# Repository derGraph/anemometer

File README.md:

# Ultrasonic Anemometer

This project contains the circuit and code for a ultrasonic Anemometer. The anemometer works by 4 ultrasonic Transducers where 2 of them always face each other. 2 Transducers describe one Axis, so with 4 Transducers you can measure x and y Wind components. The circuit only recieves the signal and boosts a Peak-to-Peak Sine Voltage of 50mV to a Square Wave of VCC to 0V. With the microcontroller you have to compare the time difference between the output signal, a signal of 50% Duty Cycle 40kHz and the recieved signal. Then you can calibrate your sensor with 0 wind speed. In my case i measure the Clock Cycles of an ESP8266 to get a pretty precise time.

### Circuit Description

The circuit contains of a LM324 OP-Amp and an LM393 Comperator. With these 2 IC's you can archive processing for 2 Channels. after the signal is coming from the transducer it gets biased with a VCC/2 Voltage to be in a useful working range for the later components. Then the signal is fed through a voltage follower to get a low impedance signal for the next Amplifier stage. The next stage is, as said an inverting Amplifier with a gain of 10. The gain can't be to high to have a functioning amplification. As you can see if you have signal at 40kHz the maximum gain can be 10. 

After that the signal is fed into the LM393 Comparator. Keep in mind that to get the comperator to function you have to pull the output up. In the first revision of the board  (Rev 1) there are 2 Footprints of resistors too much (R5, R14) this is fixed with Rev 2.

### Modularity

In the standard configuration of the PCB 2 Channels are set up but if you have a weaker Signal you can cut the S2_EN between 1/2 and solder 2/3. By populating R17 and R18 you can transform your 1 Stage Amplifier in a 3 Stage Amplifier.
If you need an additional Filter you can cut EN_Filter and populate the Bandpass-Filter on the backside of the PCB.

### Full Circuit

The whole circuit contains 2 Channels with the logic to implement the 3 Stage Amplifier included in the lower one. Also there is power supply and connectors to the MCU.

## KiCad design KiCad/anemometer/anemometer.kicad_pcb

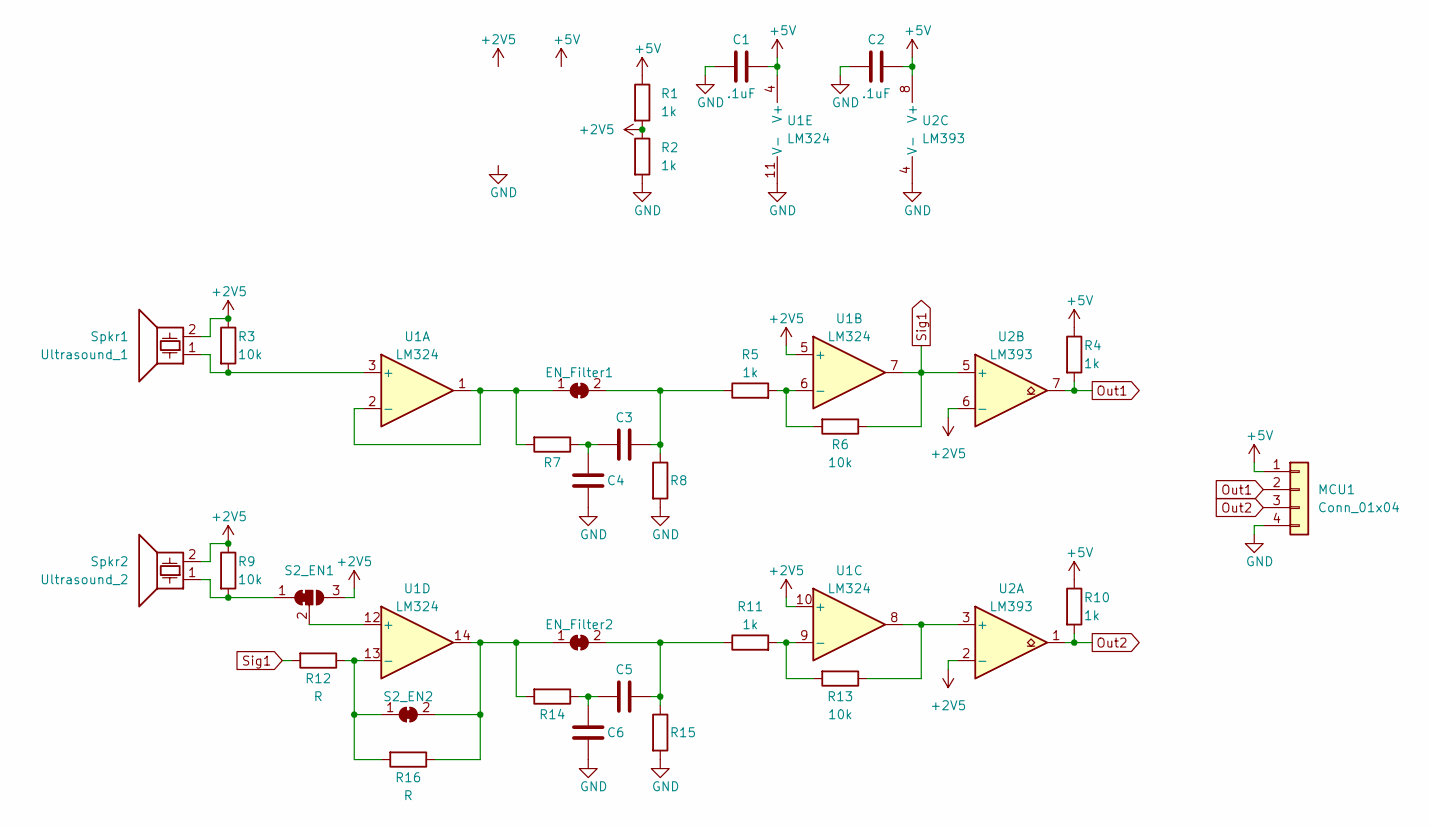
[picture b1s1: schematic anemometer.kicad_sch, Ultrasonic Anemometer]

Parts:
C1, C2: .1uF; C_0805_2012Metric_Pad1.18x1.45mm_HandSolder
C3, C4, C5, C6: C; C_0805_2012Metric_Pad1.18x1.45mm_HandSolder
EN_Filter1, EN_Filter2: SolderJumper_2_Bridged; SolderJumper-2_P1.3mm_Bridged_RoundedPad1.0x1.5mm
MCU1: Conn_01x04; JST_SH_SM04B-SRSS-TB_1x04-1MP_P1.00mm_Horizontal
R1, R2, R4, R5, R10, R11: 1k; R_0805_2012Metric_Pad1.20x1.40mm_HandSolder
R3, R6, R9, R13: 10k; R_0805_2012Metric_Pad1.20x1.40mm_HandSolder
R7, R8, R12, R14, R15, R16: R; R_0805_2012Metric_Pad1.20x1.40mm_HandSolder
S2_EN1: SolderJumper_3_Bridged12; SolderJumper-3_P1.3mm_Bridged2Bar12_RoundedPad1.0x1.5mm_Num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
S2_EN2: SolderJumper_2_Bridged; SolderJumper-2_P1.3mm_Bridged_RoundedPad1.0x1.5mm
Spkr1: Ultrasound_1; JST_SH_SM02B-SRSS-TB_1x02-1MP_P1.00mm_Horizontal
Spkr2: Ultrasound_2; JST_SH_SM02B-SRSS-TB_1x02-1MP_P1.00mm_Horizontal
U1: LM324; SOIC-14_3.9x8.7mm_P1.27mm
U2: LM393; SOIC-8_3.9x4.9mm_P1.27mm

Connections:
+2V5: R1.2, R2.1, R3.1, R9.1, S2_EN1.3 (B), Spkr1.2, Spkr2.2, U1.5 (+), U1.10 (+), U2.2 (-), U2.6 (-)
+5V: C1.1, C2.1, MCU1.1, R1.1, R4.1, R10.1, U1.4 (V+), U2.8 (V+)
GND: C1.2, C2.2, C4.2, C6.2, MCU1.4, R2.2, R8.2, R15.2, U1.11 (V-), U2.4 (V-)
unnamed: C3.2, C4.1, R7.1
unnamed: C5.2, C6.1, R14.1
unnamed: EN_Filter1.1 (A), R7.2, U1.1, U1.2 (-)
unnamed: C3.1, EN_Filter1.2 (B), R5.1, R8.1
unnamed: EN_Filter2.1 (A), R14.2, R16.1, S2_EN2.2 (B), U1.14
unnamed: C5.1, EN_Filter2.2 (B), R11.1, R15.1
unnamed: R9.2, S2_EN1.1 (A), Spkr2.1
unnamed: S2_EN1.2 (C), U1.12 (+)
unnamed: R12.1, R16.2, S2_EN2.1 (A), U1.13 (-)
unnamed: R3.2, Spkr1.1, U1.3 (+)
unnamed: R5.2, R6.2, U1.6 (-)
unnamed: R11.2, R13.2, U1.9 (-)
unnamed: R13.1, U1.8, U2.3 (+)
Out1: MCU1.2, R4.2, U2.7
Out2: MCU1.3, R10.2, U2.1
Sig1: R6.1, R12.2, U1.7, U2.5 (+)

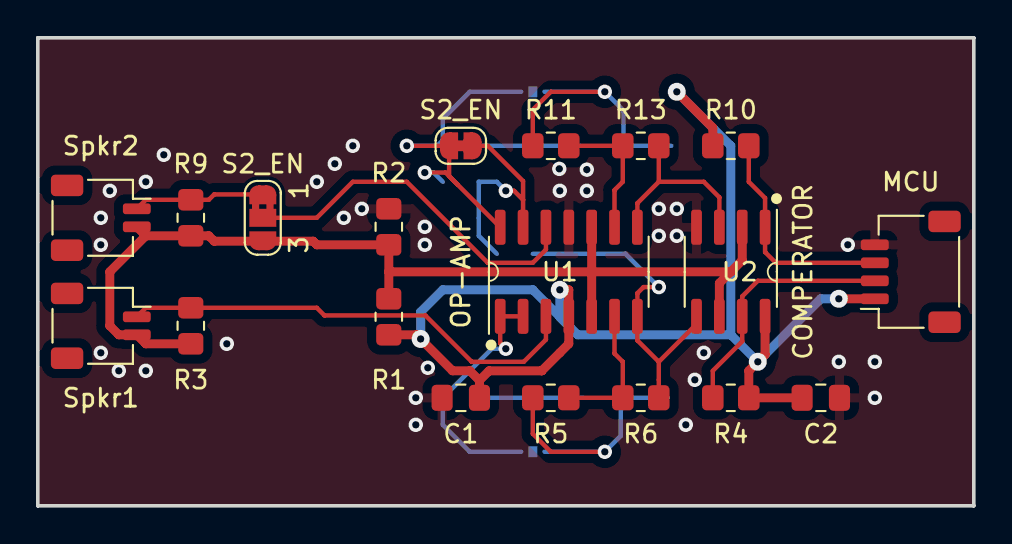
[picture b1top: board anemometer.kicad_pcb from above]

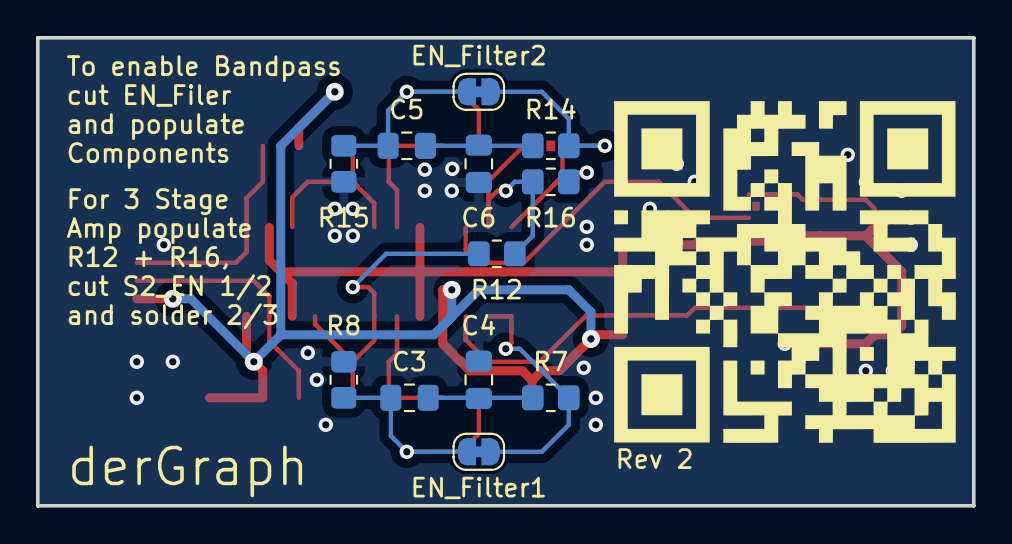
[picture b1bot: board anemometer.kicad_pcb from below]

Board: 2 copper layers, 52.0 x 26.0 mm, 31 parts (12 on the bottom side), 19 nets.

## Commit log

2024-03-22 initial commit, Rev 1
2024-03-22 Add Infos to README
2024-03-22 Board Rev 2
